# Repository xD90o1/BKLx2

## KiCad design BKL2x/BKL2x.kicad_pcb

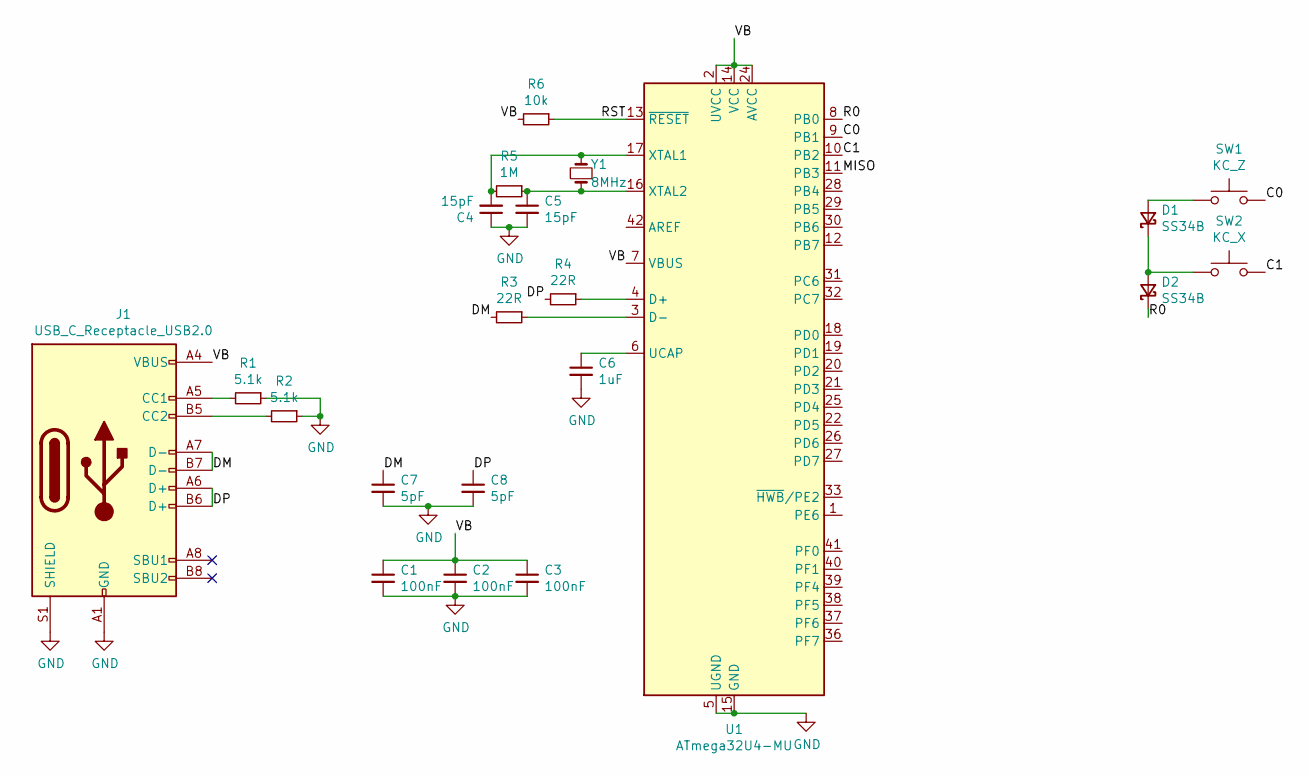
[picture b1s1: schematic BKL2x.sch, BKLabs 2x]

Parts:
C1, C2, C3: 100nF; C_0402_1005Metric
C4, C5: 15pF; C_0402_1005Metric
C6: 1uF; C_0402_1005Metric
C7, C8: 5pF; C_0402_1005Metric
D1, D2: SS34B; D_SMB
J1: USB_C_Receptacle_USB2.0; USB_C_Receptacle_XKB_U262-16XN-4BVC11
R1, R2: 5.1k; R_0402_1005Metric
R3, R4: 22R; R_0402_1005Metric
R5: 1M; R_0402_1005Metric
R6: 10k; R_0402_1005Metric
SW1: KC_Z; SW_Cherry_MX_1.00u_PCB
SW2: KC_X; SW_Cherry_MX_1.00u_PCB
U1: ATmega32U4-MU; QFN-44-1EP_7x7mm_P0.5mm_EP5.2x5.2mm
Y1: 8MHz; Crystal_SMD_HC49-SD

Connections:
/C0: SW1.2, U1.9 (PB1)
/C1: SW2.2, U1.10 (PB2)
/DM: C7.1, J1.A7 (D-), J1.B7 (D-), R3.2
/DP: C8.1, J1.A6 (D+), J1.B6 (D+), R4.2
/MISO: U1.11 (PB3)
/R0: D2.1 (K), U1.8 (PB0)
/RST: R6.1, U1.13 (~RESET)
/VB: C1.1, C2.1, C3.1, J1.A4 (VBUS), J1.A9 (VBUS), J1.B4 (VBUS), J1.B9 (VBUS), R6.2, U1.2 (UVCC), U1.7 (VBUS), U1.14 (VCC), U1.24 (AVCC), U1.34 (VCC), U1.44 (AVCC)
GND: C1.2, C2.2, C3.2, C4.1, C5.2, C6.2, C7.2, C8.2, J1.A1 (GND), J1.A12 (GND), J1.B1 (GND), J1.B12 (GND), J1.S1 (SHIELD), R1.1, R2.1, U1.5 (UGND), U1.15 (GND), U1.23 (GND), U1.35 (GND), U1.43 (GND), U1.45 (GND)
unnamed: C4.2, R5.2, U1.17 (XTAL1), Y1.2
unnamed: C5.1, R5.1, U1.16 (XTAL2), Y1.1
unnamed: C6.1, U1.6 (UCAP)
unnamed: D1.1 (K), D2.2 (A), SW2.1
unnamed: D1.2 (A), SW1.1
unnamed: J1.A5 (CC1), R1.2
unnamed: J1.B5 (CC2), R2.2
unnamed: R3.1, U1.3 (D-)
unnamed: R4.1, U1.4 (D+)

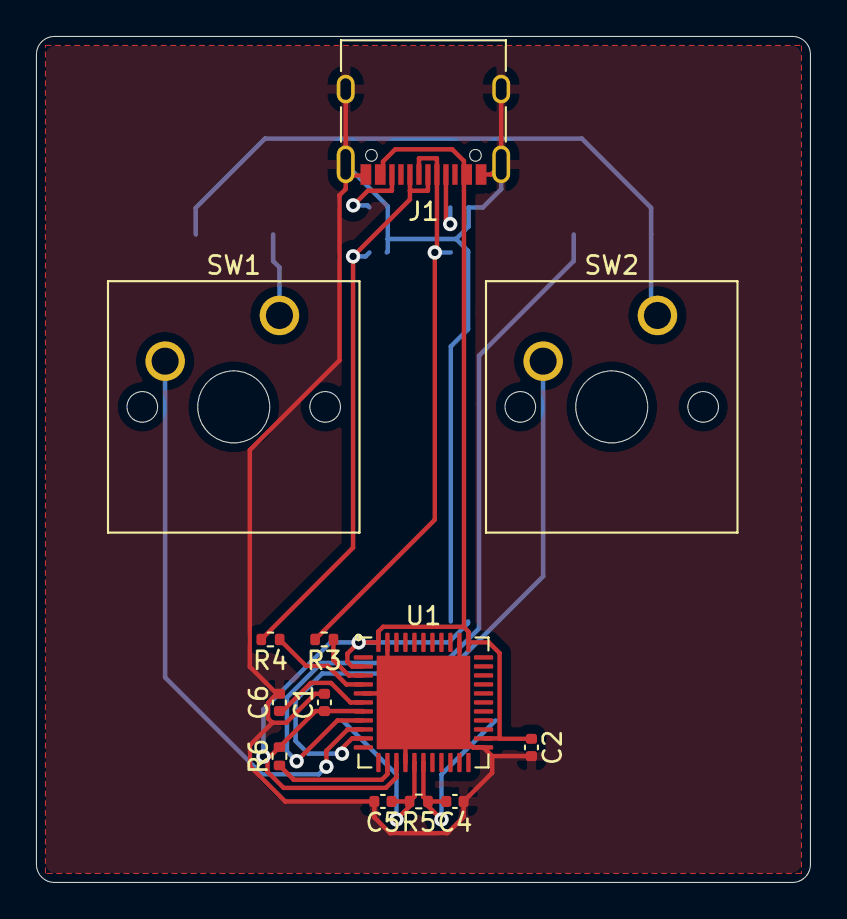
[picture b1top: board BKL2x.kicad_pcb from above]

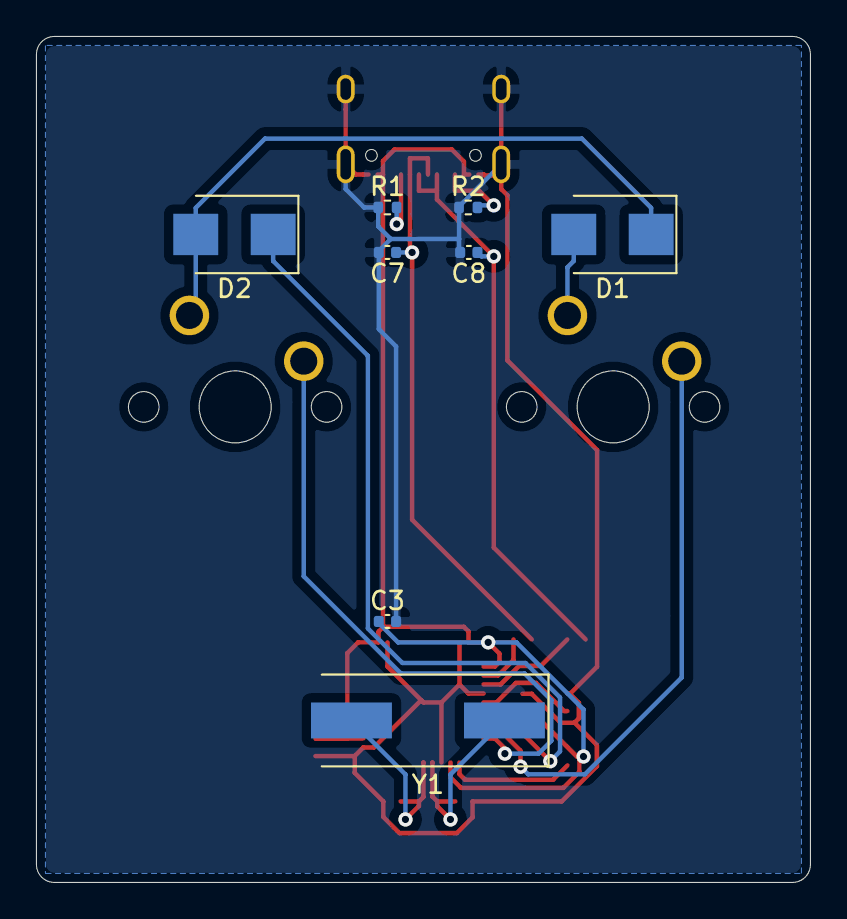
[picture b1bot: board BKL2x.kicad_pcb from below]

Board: 2 copper layers, 43.0 x 47.0 mm, 21 parts (8 on the bottom side), 17 nets.

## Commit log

2024-08-07 Preprod -> Prod
2024-08-07 Remove directoried files
2024-08-07 Directoried Files
2024-08-07 Preproduction Files Upload
